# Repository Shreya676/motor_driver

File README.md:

# Motor Driver Circuit Explanation

This circuit utilizes the L293D to control the direction of two DC motors based on digital input signals. It also includes a 5V regulator for powering the control logic and a power indicator LED.

## Components

* **U1: L293D - Quadruple Half-H Driver:** An integrated circuit containing four half-H bridge drivers, enabling bidirectional control of DC motors.
    * **1A, 2A, 3A, 4A (Input Pins):** Control the output states of the respective half-H bridges.
    * **1Y, 2Y, 3Y, 4Y (Output Pins):** Connect to the terminals of the motors.
    * **EN1,2 (Enable Pins 1 & 2):** Enable/disable the first two drivers (controlling outputs 1Y and 2Y).
    * **EN3,4 (Enable Pins 3 & 4):** Enable/disable the last two drivers (controlling outputs 3Y and 4Y).
    * **VCC1 (Pin 16):** Logic supply voltage (5V).
    * **VCC2 (Pin 8):** Motor supply voltage.
    * **GND (Pins 4, 5, 12, 13):** Ground connections.

* **U3: L7805 - 5V Voltage Regulator:** A linear regulator that provides a stable 5V output for the logic circuitry.
    * **IN (Pin 1):** Input for the higher voltage supply.
    * **GND (Pin 2):** Ground connection.
    * **OUT (Pin 3):** Regulated 5V output (**PWR\_FLAG**).

* **J1: Conn\_01x04\_Pin - Control Input Connector:** A 4-pin connector for applying digital control signals to the L293D.

* **J2: Screw\_Terminal\_01x02 - Motor Power Input:** A 2-pin screw terminal for connecting the higher voltage power supply for the motors and the input of the L7805.

* **J3: Screw\_Terminal\_01x02 - Motor Output 1:** A 2-pin screw terminal for connecting the first motor.

* **J4: Screw\_Terminal\_01x02 - Motor Output 2:** A 2-pin screw terminal for connecting the second motor.

* **D1: LED - Power Indicator:** An LED that illuminates when the 5V power supply is active.

* **R1: 1kΩ Resistor:** A current-limiting resistor for the power indicator LED.

* **PWR\_FLAG:** Net label for the regulated 5V power supply rail.

* **GND:** Net label for the common ground connection.

## Working Principle

1.  **Logic Power:** A higher DC voltage is supplied to **J2**. The **L7805 (U3)** regulates this voltage to 5V (**PWR\_FLAG**), powering the control logic of the **L293D (VCC1)**. The **LED (D1)** indicates the presence of this 5V.

2.  **Motor Power:** The higher DC voltage from **J2** also powers the motor driving stage of the **L293D (VCC2)**.

3.  **Control Inputs:** Digital signals applied to **J1** are fed into the input pins (1A, 2A, 3A, 4A) and enable pins (EN1,2, EN3,4) of the **L293D**.

4.  **Enabling Motors:** To drive a motor connected to **J3** or **J4**, the corresponding enable pin(s) on the **L293D** must be high.

5.  **Direction Control:** The logic levels on the input pins (e.g., 1A and 2A for the motor at **J3**) determine the direction of current flow through the motor, thus controlling its rotation direction. The **L293D** internally switches the power to the motor based on these inputs.

6.  **Motor Output:** The **L293D** outputs the controlled power to the motors connected at **J3** and **J4**, allowing for bidirectional control of two independent DC motors.

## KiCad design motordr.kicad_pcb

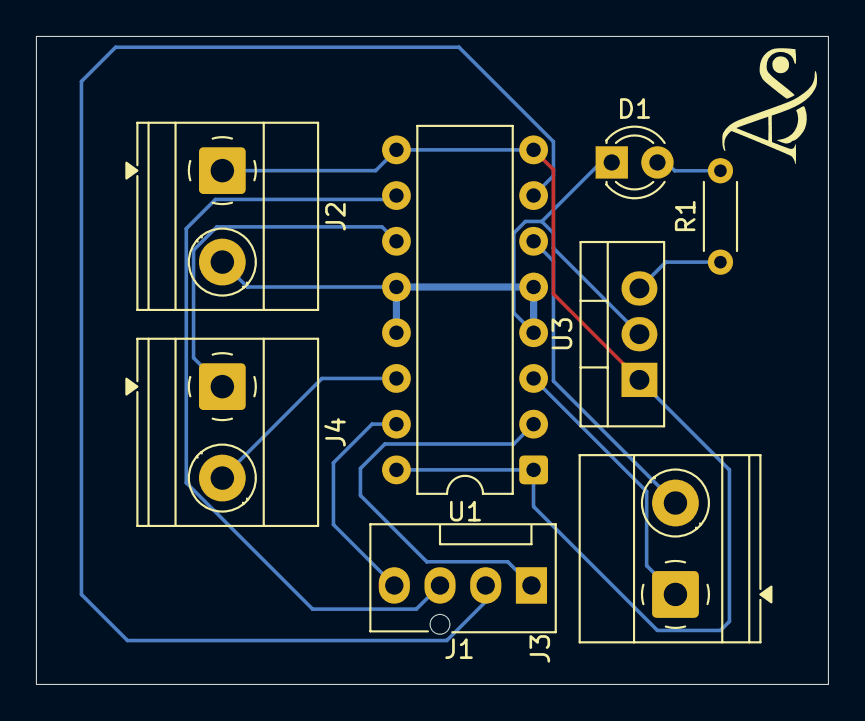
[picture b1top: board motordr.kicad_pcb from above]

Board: 2 copper layers, 44.0 x 36.0 mm, 8 parts (0 on the bottom side), 12 nets.

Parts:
D1: LED; LED_D3.0mm
J1: Conn_01x04_Pin; FanPinHeader_1x04_P2.54mm_Vertical
J2, J3: MOTOR1; TerminalBlock_Phoenix_MKDS-1,5-2-5.08_1x02_P5.08mm_Horizont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
J4: Screw_Terminal; TerminalBlock_Phoenix_MKDS-1,5-2-5.08_1x02_P5.08mm_Horizont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
R1: 1k; R_Axial_DIN0204_L3.6mm_D1.6mm_P5.08mm_Horizontal
U1: L293D; DIP-16_W7.62mm
U3: L7805; TO-220-3_Vertical

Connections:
GND: D1.1 (K), J2.2, U1.4 (GND), U1.5 (GND), U1.12 (GND), U1.13 (GND), U3.2 (GND)
unnamed: D1.2 (A), R1.2
unnamed: J1.1, U1.2 (1A)
unnamed: J1.2, U1.7 (2A)
unnamed: J1.3, U1.10 (3A)
unnamed: J1.4, U1.15 (4A)
unnamed: J2.1, U1.1 (EN1,2), U1.8 (VCC2), U1.9 (EN3,4), U1.16 (VCC1), U3.1 (IN)
unnamed: J3.1, U1.3 (1Y)
unnamed: J3.2, U1.6 (2Y)
unnamed: J4.1, U1.11 (3Y)
unnamed: J4.2, U1.14 (4Y)
unnamed: R1.1, U3.3 (OUT)

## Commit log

2025-04-28 initial setup
2025-04-28 motor driver ckt
2025-04-28 added pcb
